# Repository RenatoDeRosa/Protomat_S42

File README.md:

# Protomat_S42
Questa repository punta a diffondere le competenze necessarie a operare macchinari della lpkf protomat, in particolare in questo documento discuteremo della protomat S42,
macchinario a controllo numerico per la prototipazione di circuiti stampati, e ai software a questo corredati, quali, CircuitCam software di CAM(Computer Aided Manufacturing) e
a Boardmaster software utilizzato per operare il macchinario.

Il macchinario inizialmente si trovava in stato di inutilizzo, a causa della non operabilità dell'asse Z rendendo il macchinario inutilizzabile, grazie alla coordinazione di vari professori
che mi hanno permesso di assentarmi durate determinate ore di lezione, ho avuto la possibilità di tentare e di riuscire a portare in vita il macchinario.

## Il documento si divide in 3 punti principali
   __1. Funzionamento Hardware e componenti che consentono l'operabilità del macchinario, e come è stato diagnosticato il problema__
   
   __2. Funzionamento e utilizzo dei software principali (BM e CircuitCam)__
   
   __3. Design e Prototipazione di una scheda STM32, seguendo le linee guida del produttore__

# Struttura e Funzionamento base del macchinario
   ## Struttura testa e switch di limite
   Qui possiamo vedere come il funzionamento base della macchina sia dettato dagli switch di limite che vanno a settare i parametri di base per le assi X e Y durante l'inizzializzazione della macchina, possiamo anche
   vedere come l'asse Z al contrario delle assi X e Y è azionata da un solenoide che ha la funzione di abbassare la struttura del mandrino, successivamente per avere un movimento ascensionale
   della struttura si utilizza un sistema composto da una molla in acciaio con trazione regolabile questo perchè c'è la possibilità di montare una telecamera che facilità
   l'utilizzo della macchina e rende possibile la realizzazione di PCB a doppio strato tramite il sistema (di cui parleremo in seguito) di buchi referenziali

   ## Struttura di movimento delle assi
   Le assi sono controllare da 2 motori passo-passo COD. C9783-9212K, che vanno a controllare i due assi ,tramite un meccanismo a vite a ricircolo di sfere(Ball Screw) e a delle guide lineari, motori passo-passo di ricambio sono disponibili a un prezzo molto contenuto (intorno ai 100 euro cad.) anche se è improbabile una problematica in questi ultimi

## Struttura di protezione e isolamento acustico, aspiratore e telecamera
   La macchina ha vari optional tra cui :
  ### Custodia di protezione e isolamento acustico
   Una custodia che funge da protezione e da isolante acustico, abbiamo la fortuna di avere una macchina con questo tipo di optional
## Telecamera per creazione di buchi referenziali
   purtroppo per quanto riguarda  la telecamera non ne siamo in possesso
   la funzione della telecamera può essere facilmente sostituito da una telecamera generica USB per gestire l'offset della telecamera ed averla
   perfettamente all'ineata alla punta (cosa che andremo a montare e trattare successivamente)

## Aspiratore polveri di vetronite (FR4)
   Mentre la telecamera è facilmente sostituibile con soluzioni relativamente economiche, l'aspiratore dovendo filtrare materiale quale polveri di vetronite, materiale che può
   provocare danni alle vie respiratorie necessità di essere equipaggiato con filtri adatti al tipo di polveri che andrà a rimuovere, sembrerebbe essere sostituibile con un 
   JetStream Dust Collector by quatro, l'unità originale sembrerebbe essere un rebrand e i filtri usati appartengono a questa casa produttrice, ma qualsiasi estrattore con un
   sistema di filtraggio adeguato è adatto

# Software e Utilizzo base

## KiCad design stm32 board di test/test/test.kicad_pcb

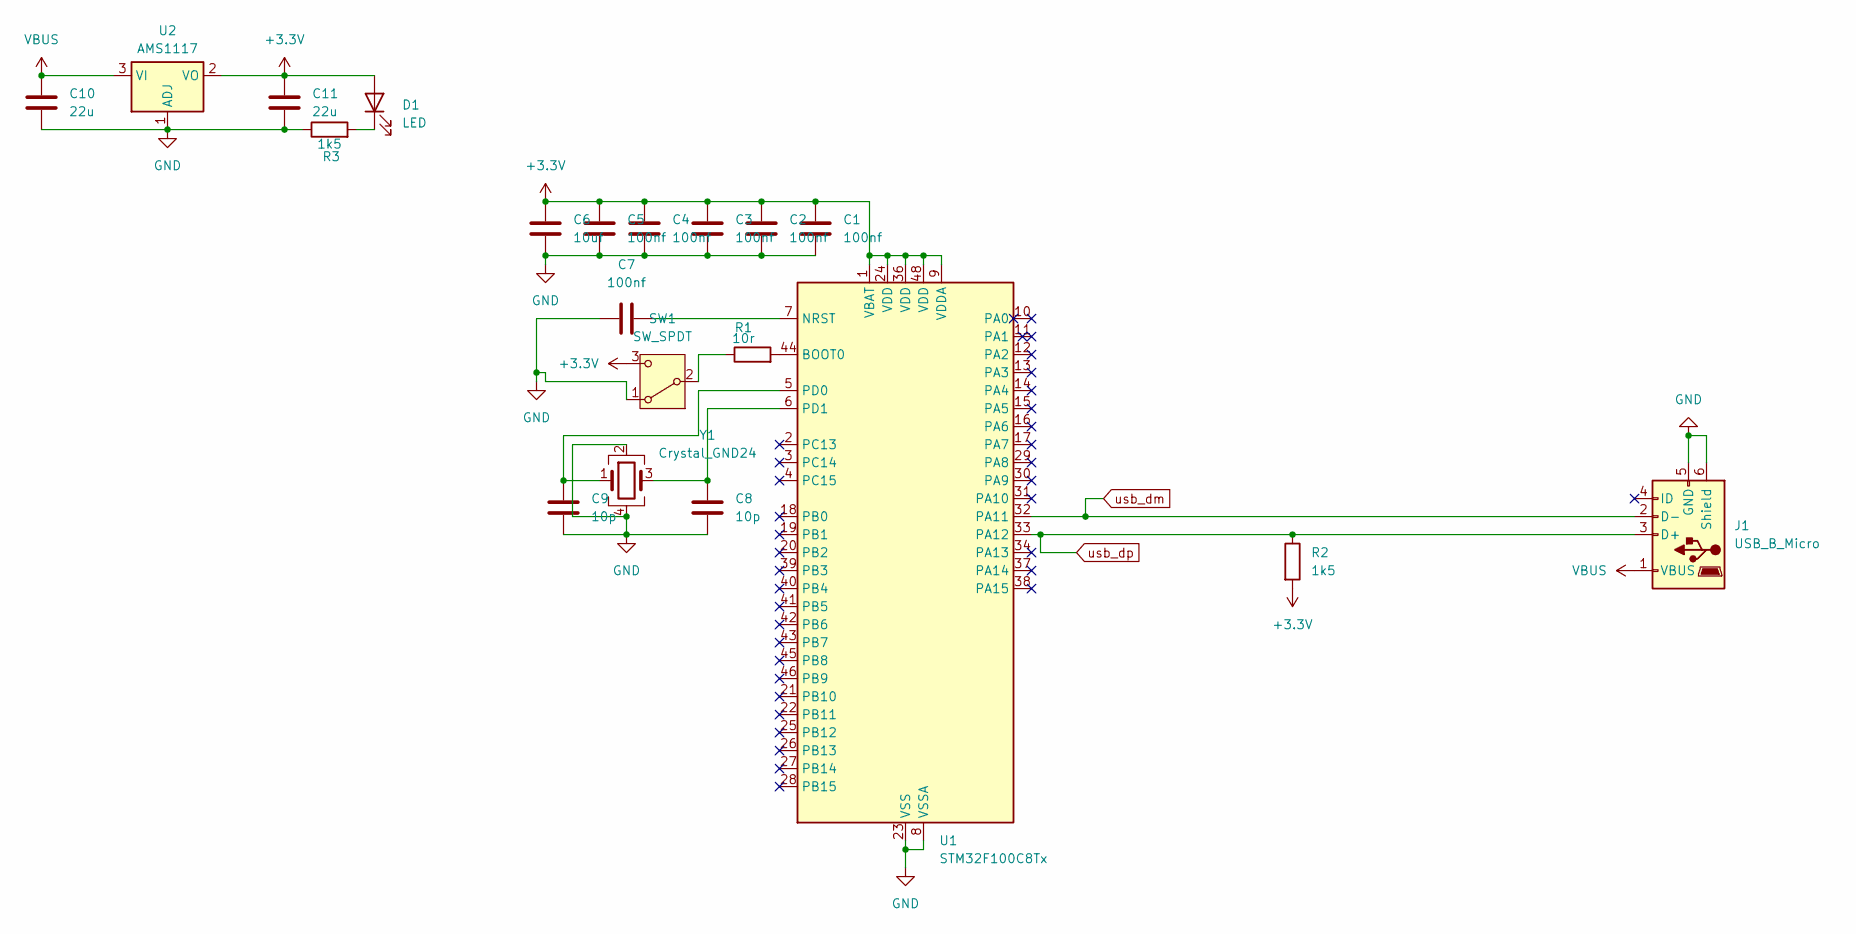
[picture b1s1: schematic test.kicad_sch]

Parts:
C1, C2, C3, C4, C5: 100nf; C_0805_2012Metric
C6: 10uf; C_0805_2012Metric
C7: 100nf; C_0603_1608Metric
C8, C9: 10p; C_0805_2012Metric
C10, C11: 22u; C_0805_2012Metric
D1: LED; C_0805_2012Metric
J1: USB_B_Micro; USB_Micro-B_Wuerth_629105150521
R1: 10r; R_0805_2012Metric
R2, R3: 1k5; R_0805_2012Metric
SW1: SW_SPDT; SW_MEC_5GSH9
U1: STM32F100C8Tx; LQFP-48_7x7mm_P0.5mm
U2: AMS1117; SOT-223-3_TabPin2
Y1: Crystal_GND24; Crystal_SMD_3225-4Pin_3.2x2.5mm_HandSoldering

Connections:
+3.3V: C1.1, C2.1, C3.1, C4.1, C5.1, C6.1, C11.1, D1.2 (A), R2.2, SW1.3 (C), U1.1 (VBAT), U1.9 (VDDA), U1.24 (VDD), U1.36 (VDD), U1.48 (VDD), U2.2 (VO)
GND: C1.2, C2.2, C3.2, C4.2, C5.2, C6.2, C7.1, C8.2, C9.2, C10.2, C11.2, J1.5 (GND), J1.6 (Shield), R3.1, SW1.1 (A), U1.8 (VSSA), U1.23 (VSS), U1.35 (VSS), U1.47 (VSS), U2.1 (ADJ), Y1.2, Y1.4
unnamed: D1.1 (K), R3.2
unnamed: R1.1, SW1.2 (B)
unnamed: R1.2, U1.44 (BOOT0)
unnamed: C7.2, U1.7 (NRST)
unnamed: C9.1, U1.5 (PD0), Y1.1
unnamed: C8.1, U1.6 (PD1), Y1.3
VBUS: C10.1, J1.1 (VBUS), U2.3 (VI)
usb_dm: J1.2 (D-), U1.32 (PA11)
usb_dp: J1.3 (D+), R2.1, U1.33 (PA12)

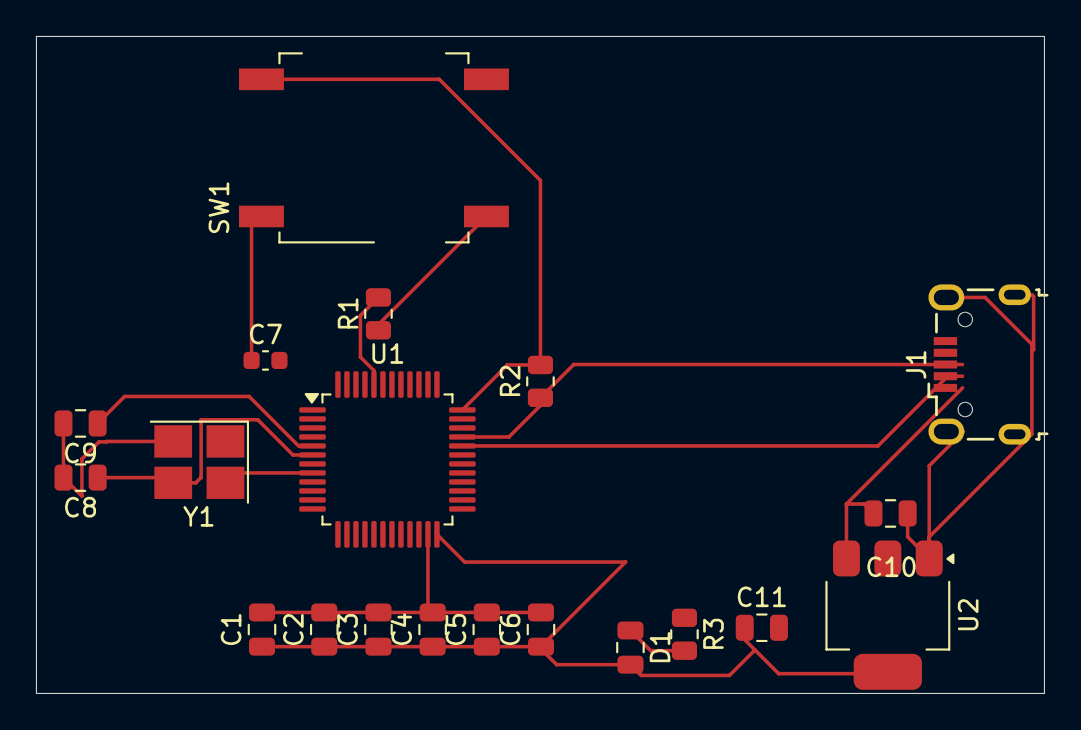
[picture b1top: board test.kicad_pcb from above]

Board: 2 copper layers, 56.0 x 36.5 mm, 20 parts (0 on the bottom side), 11 nets.
